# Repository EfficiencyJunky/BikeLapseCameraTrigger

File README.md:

# BikeLapseCameraTrigger Overview

The BikeLapse Camera Trigger is an Arduino based system for using distance (number of wheel rotations on a bike) to trigger a camera shutter release (as opposed to TimeLapse which uses time). It's part of a larger platform called BikeLapse.com that seeks to make it fun and easy to create a virtual catalog of bike rides (or other adventure activities). Plus it's entirely free and open source.

This repository is home to everything you should need to build your own BikeLapse Camera Trigger as seen in the animated GIF above and demo videos below. Once you've made the Camera Trigger hardware, visit the BikeLapse.com GitHub repo to learn how to clone the repo (you'll need to modify a couple things of course) and enable your own BikeLapse style website hosted for free on GitHub pages. (it should take less than an hour to get your own instance up and running thanks to the magic of Github).

# DEMOS
Here's a video showing how the BikeLapse camera trigger works and what it is used for
https://www.youtube.com/watch?v=APi-ftsqltU

Here's a demo of a video that was made by stitching together all of the images captured while using the BikeLapse Camera Trigger
https://www.youtube.com/watch?v=EekVvGeG3ls

To see the virtual bike ride version where the video is geo-synchronized to a map...check out https://bikelapse.com

# PROJECT DESCRIPTION AND BUILD INSTRUCTIONS
Visit http://turnerkirk.com/bikelapse for a thorough description of this project and information on how to make your own.

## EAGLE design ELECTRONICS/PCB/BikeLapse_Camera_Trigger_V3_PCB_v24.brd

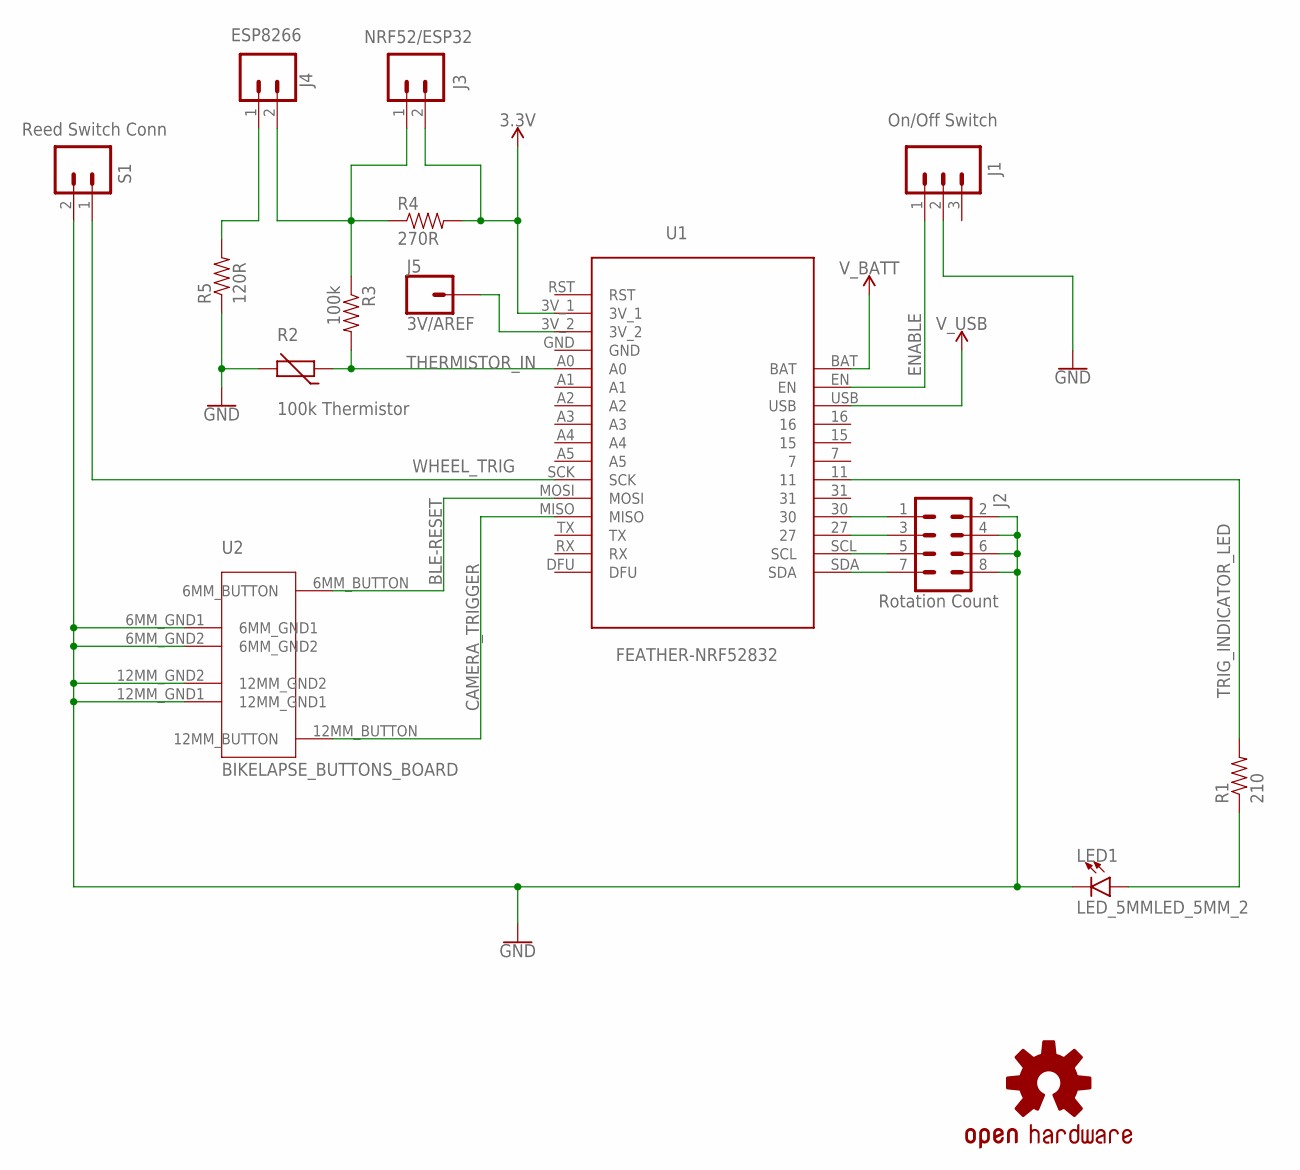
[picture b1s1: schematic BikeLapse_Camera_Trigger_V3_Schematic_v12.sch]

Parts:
J1: On/Off Switch; 1X03_RA_PTH
J2: Rotation Count; 2X4
J3: NRF52/ESP32; 1X02
J4: ESP8266; 1X02
J5: 3V/AREF; 1X01
LED1: LED_5MMLED_5MM_2; LEDRD254W60D565H860B
LOGO1: OSHW-LOGOL; OSHW-LOGO-L
R1: 210; SPARKFUN-RESISTORS_AXIAL-0.4
R2: 100k Thermistor; RS-2,5-SINGLE_PIN
R3: 100k; SPARKFUN-RESISTORS_AXIAL-0.4
R4: 270R; SPARKFUN-RESISTORS_AXIAL-0.4
R5: 120R; SPARKFUN-RESISTORS_AXIAL-0.4
S1: Reed Switch Conn; 1X02_RA_PTH
U1: FEATHER-NRF52832
U2: BIKELAPSE_BUTTONS_BOARD

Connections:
3.3V: J3.2, R4.P$2 (2), U1.3V_1
BLE-RESET: U1.MOSI, U2.6MM_BUTTON
CAMERA_TRIGGER: U1.MISO, U2.12MM_BUTTON
ENABLE: J1.1, U1.EN
GND: J1.2, J2.2, J2.4, J2.6, J2.8, LED1.K (C), R2.2, R5.P$1 (1), S1.2, U1.GND, U2.6MM_GND1, U2.6MM_GND2, U2.12MM_GND1, U2.12MM_GND2
unnamed: J2.3, U1.27
unnamed: J2.1, U1.30
unnamed: J2.5, U1.SCL
unnamed: J2.7, U1.SDA
unnamed: J5.1, U1.3V_2
unnamed: J4.1, R5.P$2 (2)
unnamed: J3.1, J4.2, R3.P$1 (1), R4.P$1 (1)
unnamed: LED1.A, R1.P$1 (1)
THERMISTOR_IN: R2.1, R3.P$2 (2), U1.A0
TRIG_INDICATOR_LED: R1.P$2 (2), U1.11
V_BATT: U1.BAT
V_USB: U1.USB
WHEEL_TRIG: S1.1, U1.SCK

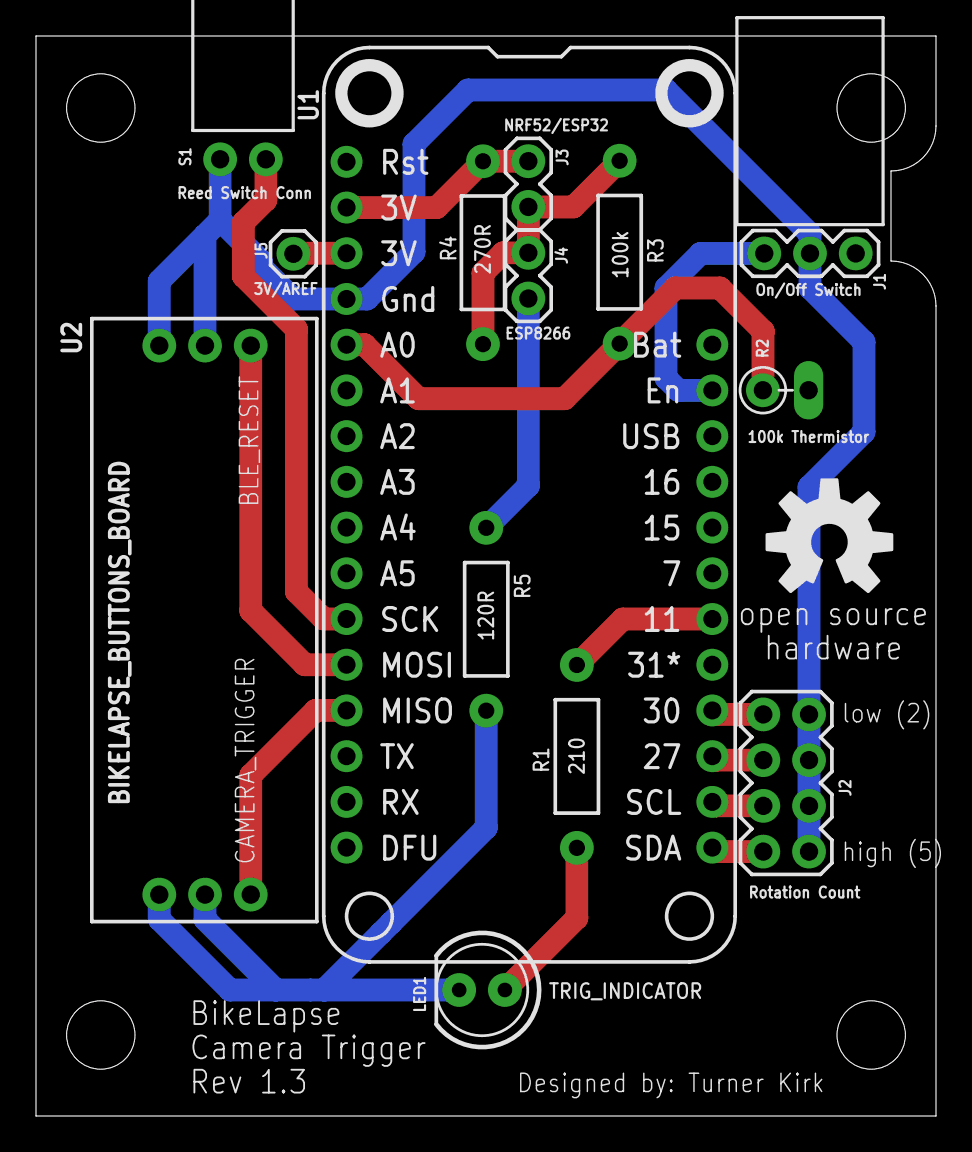
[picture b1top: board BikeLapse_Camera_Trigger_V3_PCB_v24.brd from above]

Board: 2 copper layers, 50.0 x 60.0 mm, 15 parts (0 on the bottom side), 16 nets.

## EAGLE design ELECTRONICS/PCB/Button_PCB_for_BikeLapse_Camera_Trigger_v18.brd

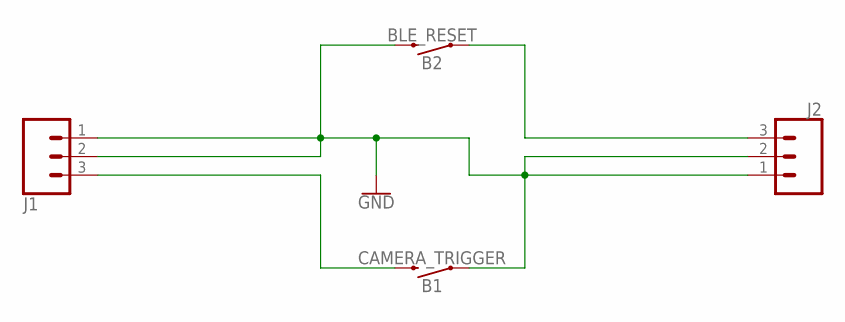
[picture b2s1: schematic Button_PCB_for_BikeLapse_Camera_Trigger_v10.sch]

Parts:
B1: CAMERA_TRIGGER; TACTILE_SWITCH_PTH_12MM
B2: BLE_RESET; TACTILE_SWITCH_PTH_6.0MM
J1, J2: 455-1750-1-ND; 1X03-MALE_HEADERS_BOTTOM

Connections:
GND: B1.1, B2.3 (2), J1.1, J1.2, J2.1, J2.2
unnamed: B2.1, J2.3
unnamed: B1.3 (2), J1.3

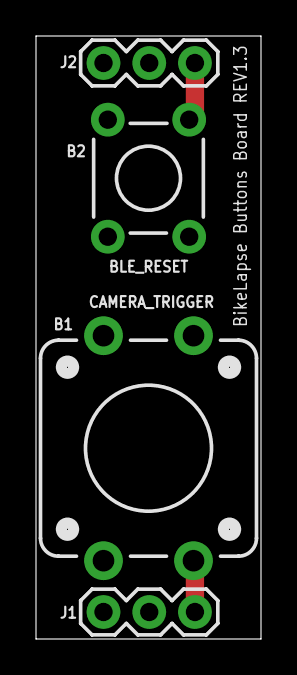
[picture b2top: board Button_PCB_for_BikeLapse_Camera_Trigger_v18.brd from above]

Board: 2 copper layers, 12.5 x 33.5 mm, 4 parts (0 on the bottom side), 3 nets.

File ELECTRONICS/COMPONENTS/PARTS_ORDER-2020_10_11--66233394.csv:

"Index","Quantity","Part Number","Manufacturer Part Number","Description","Customer Reference","Backorder","Unit Price","Extended Price"
"1","3","EG1903-ND","EG1218","SWITCH SLIDE SPDT 200MA 30V","ON/OFF SWITCH STRIAGHT","0","0.65000","$1.95"
"2","6","S9337-ND","QPC02SXGN-RC","CONN JUMPER SHORTING .100"" GOLD","JUMPER SHORTING CONNECTORS","0","0.10000","$0.60"
"3","3","563-1555-ND","MFS101D-6-Z","SWITCH SLIDE SPDT 300MA 10V","ON/OFF SWITCH R/A","0","1.09000","$3.27"
"4","2","1528-2537-ND","598","36-PIN 0.1 FEMALE HEADER- 5PK","FEMALE HEADERS - STRAIGHT","0","2.95000","$5.90"
"5","3","HDR100IMP40M-G-RA-TH-ND","HDR100IMP40M-G-RA-TH","CONN HEADER R/A 40POS 2.54MM","MALE HEADERS - R/A","0","0.79000","$2.37"
"6","6","HDR100IMP40M-G-V-TH-ND","HDR100IMP40M-G-V-TH","CONN HEADER VERT 40POS 2.54MM","MALE HEADERS - STRAIGHT","0","0.69000","$4.14"
"7","3","732-2867-ND","61900211621","CONN HSNG 2POS FEMALE 2.54MM","REED SWITCH CONNECTOR HOUSING","0","0.13000","$0.39"
"8","3","732-2699-ND","61900211021","CONN HEADER R/A 2POS 2.54MM","REED SWITCH CONNECTOR R/A HEADERS","0","0.53000","$1.59"
"9","10","S9473CT-ND","SWT25X-URTC-S01-UU-UU","CONN SOCKET 20-26AWG CRIMP TIN","REED SWITCH CONNECTOR RECEPTACLE CRIMP PINS","0","0.06600","$0.66"
"10","3","1125-1188-ND","MT4118-HR-A","LED RED DIFFUSED 5MM ROUND T/H","LED 5MM","0","0.35000","$1.05"
"11","3","210XBK-ND","MFR-25FBF52-210R","RES 210 OHM 1/4W 1% AXIAL","210 OHM RESISTOR FOR LED","0","0.10000","$0.30"
"12","3","S120CACT-ND","RNMF14FTC120R","RES 120 OHM 1/4W 1% AXIAL","120 OHM RESISTOR","0","0.10000","$0.30"
"13","3","S270CACT-ND","RNMF14FTC270R","RES 270 OHM 1/4W 1% AXIAL","270 OHM RESISTOR","0","0.10000","$0.30"
"14","3","S100KCACT-ND","RNMF14FTC100K","RES 100K OHM 1/4W 1% AXIAL","100K RESISTOR","0","0.10000","$0.30"
"15","3","430476085716-ND","430476085716","SWITCH TACTILE SPST-NO 0.05A 12V","12MM BUTTON - CAMERA_TRIGGER","0","0.49000","$1.47"
"16","3","SW406-ND","B3F-1070","SWITCH TACTILE SPST-NO 0.05A 24V","6MM BUTTON - BLE_RESET","0","0.40000","$1.20"
"","","","","","","","Subtotal","$25.79"

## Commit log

2020-04-25 added some files
2020-04-26 First Iteration of basic button logic complete
2020-04-26 removed test_code folder from public repository
2020-04-28 added bluetooth shutter release code
2020-04-28 updated LED communication to use only analogWrite and made final tweaks
2020-04-28 fixed bug where ledPin was used instead of LED_PIN in main .ino sketch
2020-08-26 Re-arranged Github repo
2020-10-12 Finished V3 version ready for ordering and building
2020-10-12 added BOM and PCB files
2020-10-12 added animated gif of Virtual Demo for BikeLapse Hardware
2020-10-12 update readme with animated gif
2020-10-13 updated BRD to have notch for battery wires
2020-10-13 updated PCB to have separate 3V/Aref pin
2020-10-14 updated BikeLapseCameraTrigger.ino to work with both nRF52 feather boards
